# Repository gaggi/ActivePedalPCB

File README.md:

# Switch-!t ActivePedalPCB
This is a custom PCB designed for the [DIY Force Feedback Pedal](https://github.com/ChrGri/DIY-Sim-Racing-FFB-Pedal). Similar to the V4 PCB from the previously mentioned repository, it is designed to accommodate all the required development and breakout boards. The PCB is built around the Waveshare [ESP32-S3-DEV-Kit-N8R8](https://www.waveshare.com/wiki/ESP32-S3-DEV-KIT-N8R8) and features only five SMD components that need to be soldered by hand.

It is intended to operate via a single USB-B connector for each pedal, powered by a single Meanwell GST360B36-C6P power supply. The power supply can be daisy-chained from one pedal to another. Additionally, the PCB includes space for an optional N7805 step-down converter, enabling all electronics to be powered directly by the power supply. If you choose to solder the N7805, ensure that the 5V connection from the JST-XH header labeled "USB" to the USB-C plug remains unconnected.

# Soldering you PCB
The PCB is designed to allow sub-boards to be attached using female headers or soldered directly to the board. If you opt for direct soldering, follow these steps:
1. Front Side: Start by soldering the SMD components, then solder the pin headers for the ESP32-S3-DEV-KIT-N8R8.
2. Back Side: Solder the ADS1256 module.
3. Front Side: ESP32-S3-DEV-KIT-N8R8: Attach it to the already soldered headers.
   
Once these steps are complete, you can solder all remaining components to the PCB.

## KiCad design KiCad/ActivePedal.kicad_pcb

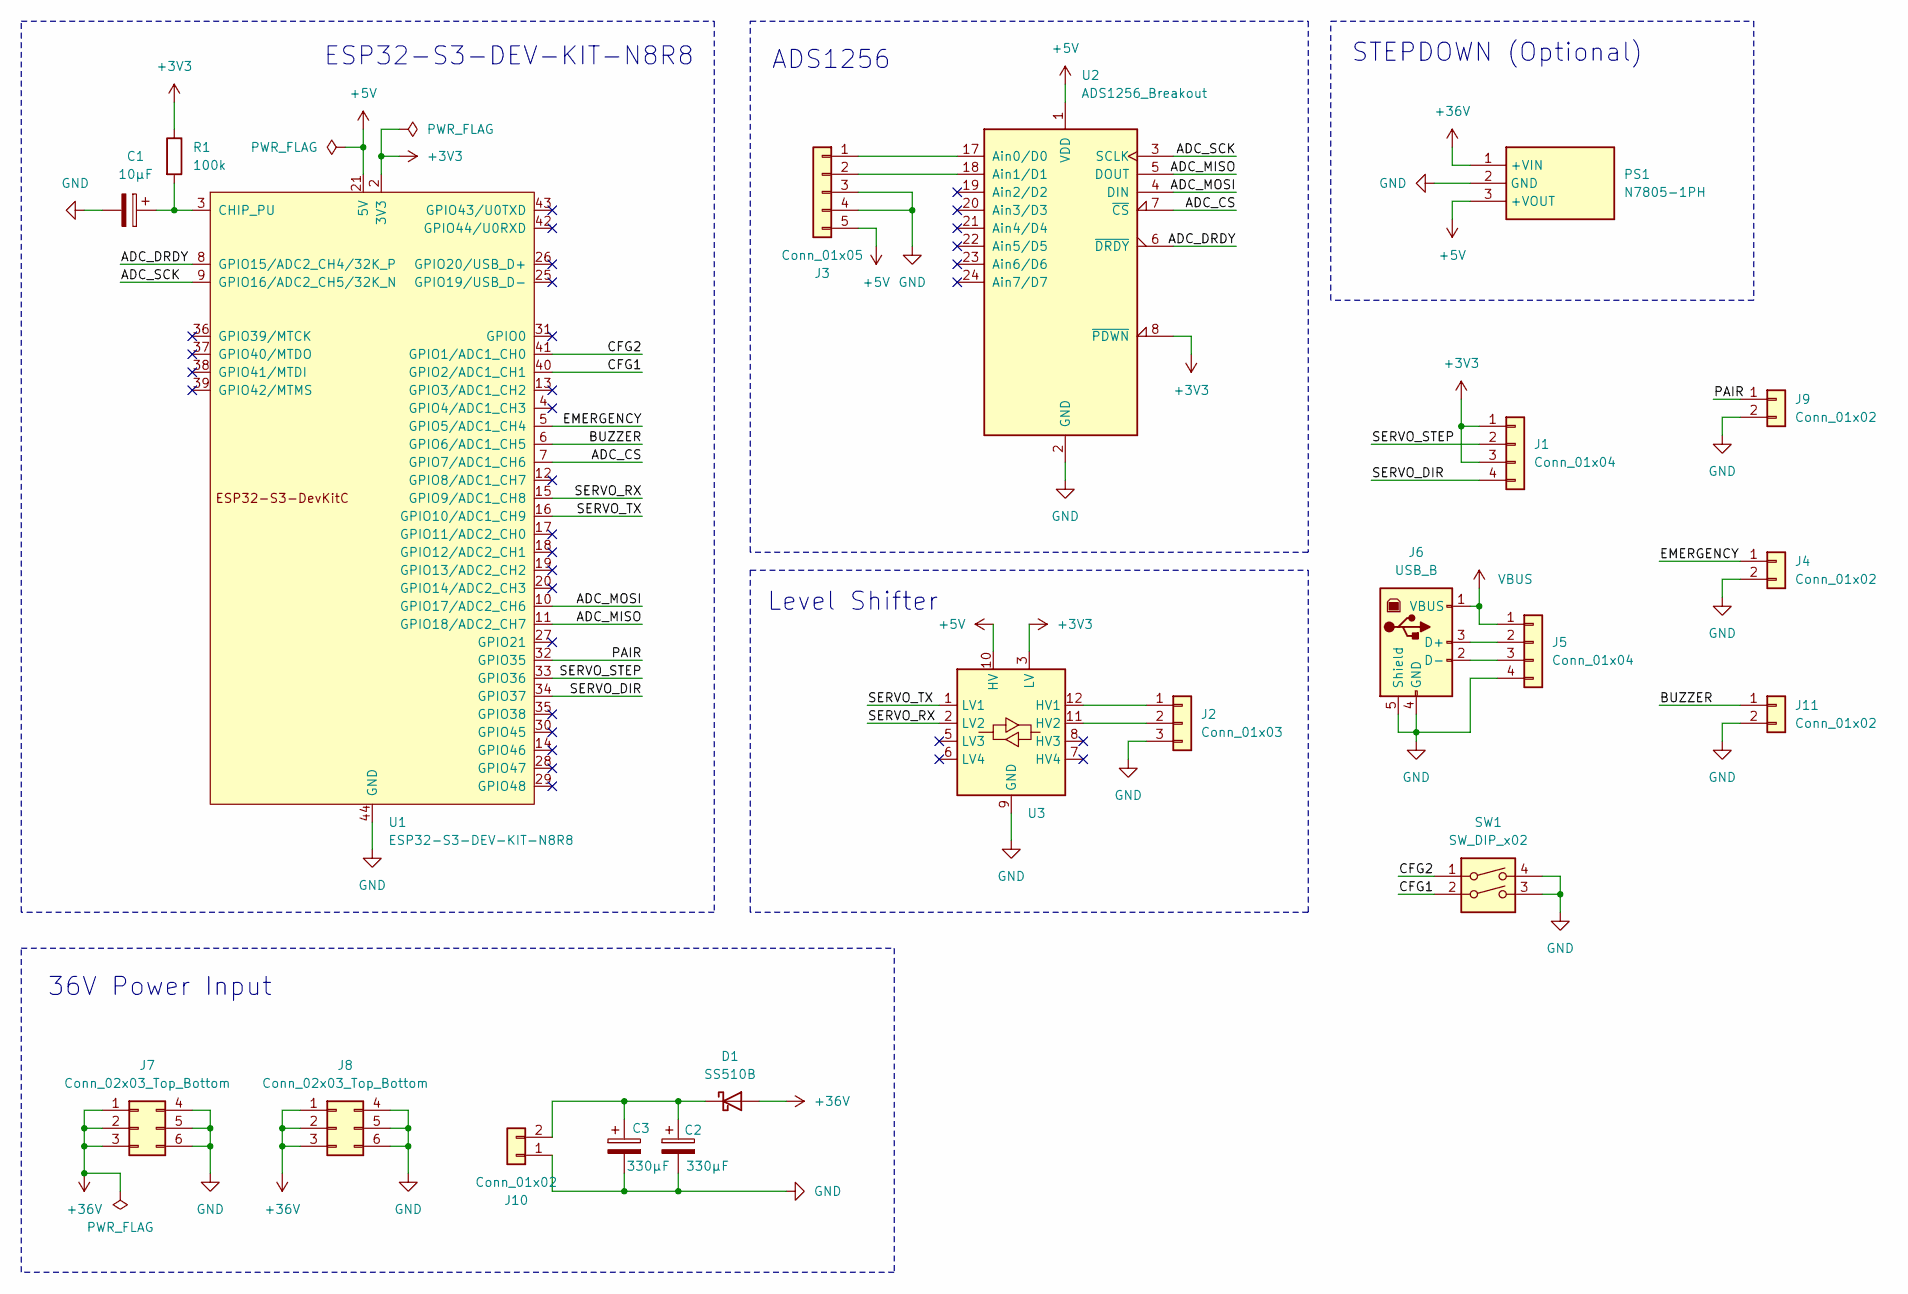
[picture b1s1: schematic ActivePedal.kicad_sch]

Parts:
C1: 10µF; CP_Elec_6.3x5.9; Mouser Part Number 710-865080743010
C2, C3: 330µF; CP_Elec_10x10; Mouser Part Number 710-865230657014
D1: SS510B; D_SMA-SMB_Universal_Handsoldering; Mouser Part Number 621-SDT5A50SAF-13
J1, J5: Conn_01x04; JST_XH_B4B-XH-A_1x04_P2.50mm_Vertical; Mouser Part Number 306-B4BXH2TV4LFSN
J2: Conn_01x03; JST_XH_B3B-XH-A_1x03_P2.50mm_Vertical; Mouser Part Number 306-BH3BXH2LFSN
J3: Conn_01x05; JST_XH_B5B-XH-A_1x05_P2.50mm_Vertical
J4, J9, J11: Conn_01x02; JST_XH_B2B-XH-A_1x02_P2.50mm_Vertical; Mouser Part Number 306-B2BXH2TV4LFSN
J6: USB_B; USB_B_OST_USB-B1HSxx_Horizontal; Mouser Part Number 640-USB1030-GF-P-B-B
J7, J8: Conn_02x03_Top_Bottom; Molex_Mini-Fit_Jr_5569-06A2_2x03_P4.20mm_Horizontal; Mouser Part Number 538-26-01-3116
J10: Conn_01x02; AMASS_XT30U-F_1x02_P5.0mm_Vertical; Mouser Part Number 306-B2BXH2TV4LFSN
PS1: N7805-1PH; N78051PH; Mouser Part Number 709-N7805-1PH
R1: 100k; R_1206_3216Metric_Pad1.30x1.75mm_HandSolder; Mouser Part Number 708-RNCF1206BTE100K
SW1: SW_DIP_x02; SW_DIP_SPSTx02_Slide_9.78x7.26mm_W7.62mm_P2.54mm; Mouser Part Number 655-1825360-1
U1: ESP32-S3-DEV-KIT-N8R8
U2: ADS1256_Breakout
U3: Levelshifter_Breakout

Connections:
+3V3: J1.1, J1.3, R1.1, U1.1 (3V3), U1.2 (3V3), U2.8 (~PDWN), U3.3 (LV)
+5V: J3.5, PS1.3 (+VOUT), U1.21 (5V), U2.1 (VDD), U3.10 (HV)
+36V: D1.2 (A), J7.1, J7.2, J7.3, J8.1, J8.2, J8.3, PS1.1 (+VIN)
/ADC_CS: U1.7 (GPIO7/ADC1_CH6), U2.7 (~CS)
/ADC_DRDY: U1.8 (GPIO15/ADC2_CH4/32K_P), U2.6 (~DRDY)
/ADC_MISO: U1.11 (GPIO18/ADC2_CH7), U2.5 (DOUT)
/ADC_MOSI: U1.10 (GPIO17/ADC2_CH6), U2.4 (DIN)
/ADC_SCK: U1.9 (GPIO16/ADC2_CH5/32K_N), U2.3 (SCLK)
/BUZZER: J11.1, U1.6 (GPIO6/ADC1_CH5)
/CFG1: SW1.2, U1.40 (GPIO2/ADC1_CH1)
/CFG2: SW1.1, U1.41 (GPIO1/ADC1_CH0)
/EMERGENCY: J4.1, U1.5 (GPIO5/ADC1_CH4)
/PAIR: J9.1, U1.32 (GPIO35)
/SERVO_DIR: J1.4, U1.34 (GPIO37)
/SERVO_RX: U1.15 (GPIO9/ADC1_CH8), U3.2 (LV2)
/SERVO_STEP: J1.2, U1.33 (GPIO36)
/SERVO_TX: U1.16 (GPIO10/ADC1_CH9), U3.1 (LV1)
GND: C1.2, C2.2, C3.2, J2.3, J3.3, J3.4, J4.2, J5.4, J6.4 (GND), J6.5 (Shield), J7.4, J7.5, J7.6, J8.4, J8.5, J8.6, J9.2, J10.1, J11.2, PS1.2 (GND), SW1.3, SW1.4, U1.22 (GND), U1.23 (GND), U1.24 (GND), U1.44 (GND), U2.2 (GND), U2.9 (GND), U2.10 (GND), U2.11 (GND), U2.12 (GND), U2.13 (GND), U2.14 (GND), U2.15 (GND), U2.16 (GND), U3.4 (GND), U3.9 (GND)
unnamed: C2.1, C3.1, D1.1 (K), J10.2
unnamed: J2.1, U3.12 (HV1)
unnamed: J2.2, U3.11 (HV2)
unnamed: J3.1, U2.17 (Ain0/D0)
unnamed: J3.2, U2.18 (Ain1/D1)
unnamed: J5.2, J6.3 (D+)
unnamed: J5.3, J6.2 (D-)
unnamed: C1.1, R1.2, U1.3 (CHIP_PU)
VBUS: J5.1, J6.1 (VBUS)

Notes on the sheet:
ESP32-S3-DEV-KIT-N8R8
ADS1256
36V Power Input
STEPDOWN (Optional)
Level Shifter

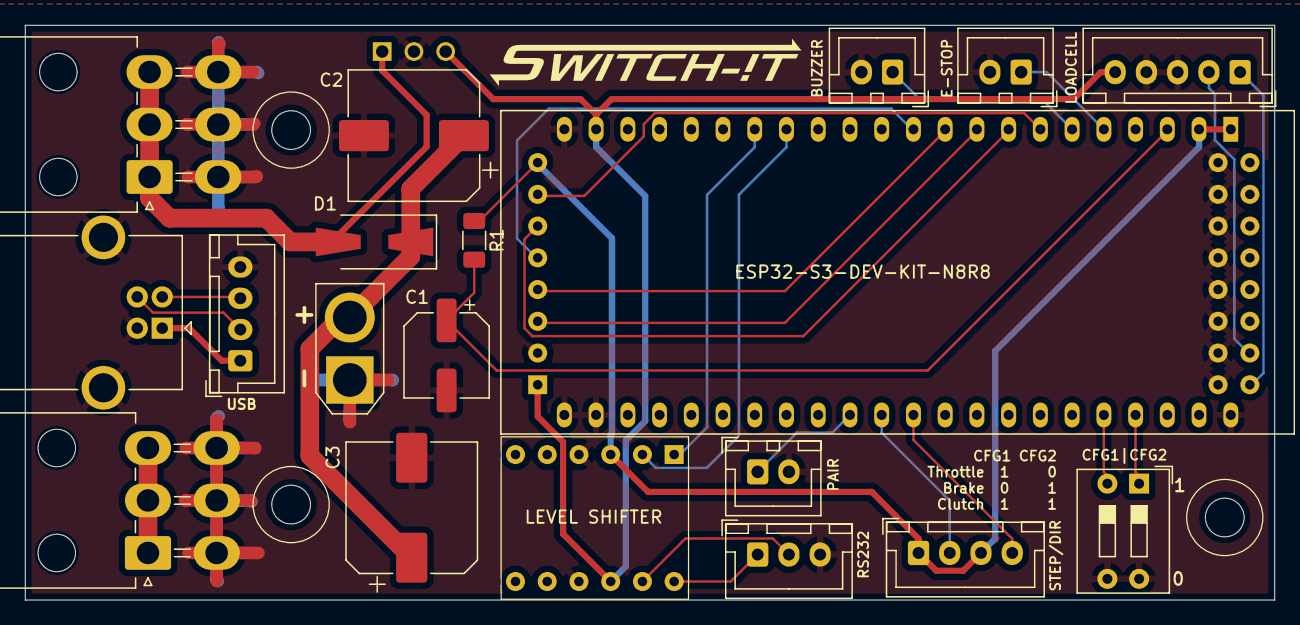
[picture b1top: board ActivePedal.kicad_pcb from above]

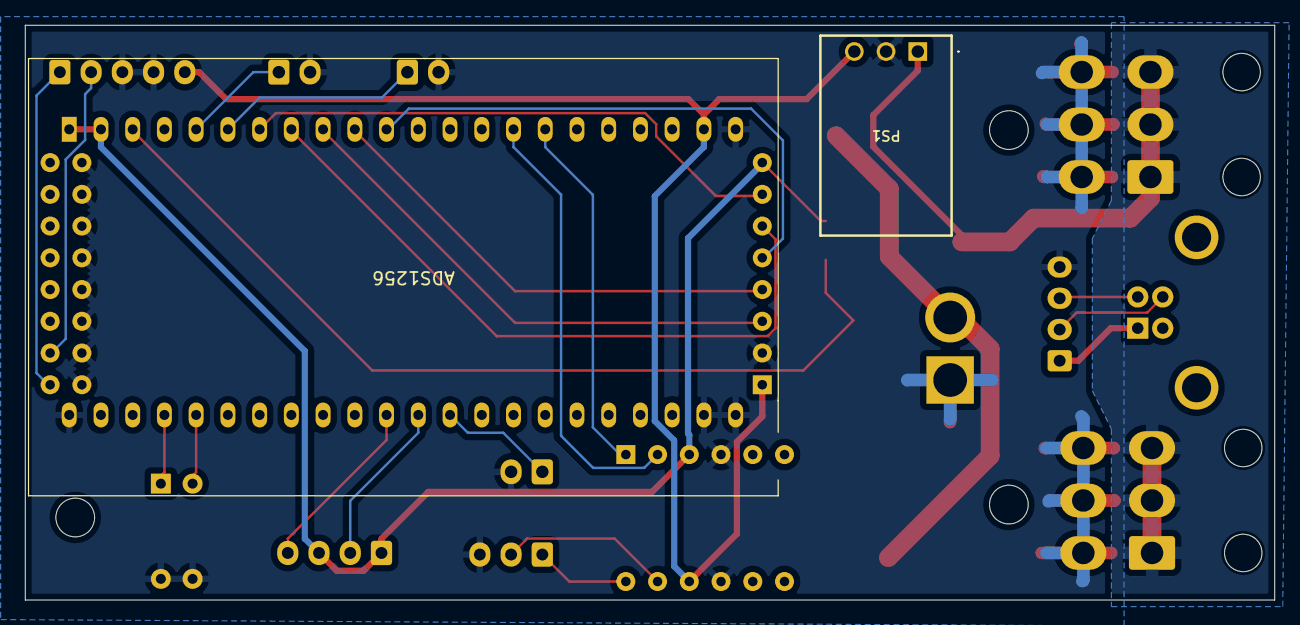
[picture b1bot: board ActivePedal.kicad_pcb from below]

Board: 2 copper layers, 100.0 x 46.0 mm, 21 parts (2 on the bottom side), 27 nets.
